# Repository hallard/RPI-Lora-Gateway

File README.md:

Raspberry PI Lora Gateway/Node for RFM92/95/96/98/69HCW Modules
===============================================================

This shield is used to hold one or two HopeRF [Lora module][4] Software with Raspbery PI plus one FM12B/RFM69CW/RFM69(H)W.
it's the parent of the small [LoRasPi][11], so please look at LoRasPi [readme][12] to see features and software links.

This board has been mainly inspired from [Uptronics][14] expansion board on which I added some features but it's not a real LoraWAN concentrator, if you need a real concentrator with multiple channels and fully compliant to LoraWan stack capabilities, please see thethingsnetwork [wiki][1] dedicated to gateways.

By the way, with Lora modules installed on this board you can have it working as a Single Channel Gateway or a LoraWan node. For testing, demo or small projects, it can be enought.

Quick features 
==============

- Placement for two RFM92/95/96/98 Lora module (IE one 868MHz and one 433MHz, or 2 channels 868MHz)
- Placement for one RFM12B/RFM69CW/RFM69(H)W classic module
- Placement for choosing single Wire, SMA, u-FL or Thru Hole PCB Mount (Right Angle Tor straight)
by Eightwood Antenna type
- Vertical Antenna placement is possible (easier to drill RPI top enclosure)
- 4 x LED for visual indication
- Each Module reset pin can be connected to a RPI GPIO

Boards arrived from ElectroDragon, all is working as expected.

Detailed Description
====================

Look at the schematics for more informations.

SPI connexion is classic (MOSI/MISO/CLK), Chip Select is CE0 for Module 1 and CE1 for Module 2. Module 3 can be choosen between CE0 and GPIO26 with on board jumper switch.

```
Raspberry PI   RFM9x Module 1
   CE0     <---->  SEL
   GPIO5   <---->  Reset (JP5)
   GPIO25  <---->  DIO0 
   GPIO24  <---->  DIO5 

Raspberry PI   RFM9x Module 2
   CE1     <---->  SEL
   GPIO6   <---->  Reset (JP6)
   GPIO16  <---->  DIO0 
   GPIO12  <---->  DIO5 

Raspberry PI   RFM69/12 Module 3
 IO26/CE0  <---->  SEL
  GPIO13   <---->  Reset (JP13)
  GPIO23   <---->  DIO0 
  GPIO12   <---->  DIO2

Raspberry PI   On Board LEDS
   GPIO4   <---->  LED 4
   GPIO17  <---->  LED 17
   GPIO18  <---->  LED 18
   GPIO19  <---->  LED 19
```

### Hardware Setup

Nothing really complicated, you can wire Reset of each module on a GPIO pin if you want to be able to hardware reset then using software, in this case put jumper on JP5 for Module 1, JP6 for Module 2 and JP13 for Module 3. JPx number is the GPIO so JP5 is for GPIO5 ;-)

If you want to use Module 1 and Module 3 you need to set JP1 (Chip Select of module 3) to IO26 since CE0 is used by Module 1.

### Software Setup

I'm working on two libraries port and Single Channel Gateway to work on Raspberry PI, links are here   

- [LMIC][15] to be LoraWan compliant.  This LMIC is working with this shield, see [readme][18] of repo.
- Excellent [RadioHead][16] twekaed library for RFM69, RFM9x modules (and lot of others). This version is working with this shield, see [readme][17] of library.
- The Things Network [Single Channel Gateway packet forwarder][24]

I forked all repos to tweak them, but since I'm not sure original authors would like to merge my changes just use my forks. 

For reference, original libraries and code are [Arduino-LIMC][21], [RadioHead-LIMC][23], [Single Channel Gateway packet forwarder][25]

### Schematic  

### Boards  
&nbsp;&nbsp; 

### Received boards 

&nbsp; 

You can order the PCB of this board [PCBs.io][13]. PCBs.io give me some reward when you order my designed boards from their site. This is pretty good, because I can use these rewards to create and design new boards and order boards for a discounted price and share new boards.

### Assembled and mounted board

Here is my testing board, as you can see, 3 modules on it    
- Module 1 (top left) Lora RFM95 868MHz
- Module 2 (bottom left) Lora RFM98 433MHz
- Module 3 (right) RFM69HW 433MHz

##License

You can do whatever you like with this design.

##Misc
See news and other projects on my [blog][2] 

[1]: https://www.thethingsnetwork.org/wiki/Hardware/Gateways/Overview
[2]: https://hallard.me
[4]: http://www.hoperf.com/rf_transceiver/lora/
[5]: https://github.com/hallard/single_chan_pkt_fwd
[6]: http://www.daveakerman.com/?p=1719
[7]: https://store.uputronics.com/index.php?route=product/product&search=lora&product_id=68
[8]: https://PCBs.io/share/zkD74
[9]: https://github.com/matthijskooijman/arduino-lmic/
[10]: https://github.com/hallard/RadioHead
[11]: https://github.com/hallard/LoRasPI
[12]: https://github.com/hallard/LoRasPI/blob/master/README.md
[13]: https://PCBs.io/share/zvxQ8
[14]: https://store.uputronics.com/index.php?route=product/product&search=lora&product_id=68

[15]: https://github.com/hallard/arduino-lmic/tree/rpi
[16]: https://github.com/hallard/RadioHead
[17]: https://github.com/hallard/RadioHead/blob/master/README.md
[18]: https://github.com/hallard/arduino-lmic/blob/rpi/README.md

[20]: https://github.com/hallard/arduino-lmic
[21]: https://github.com/matthijskooijman/arduino-lmic
[22]: https://github.com/hallard/RadioHead
[23]: http://www.airspayce.com/mikem/arduino/RadioHead/
[24]: https://github.com/hallard/single_chan_pkt_fwd
[25]: https://github.com/jlesech/single_chan_pkt_fwd

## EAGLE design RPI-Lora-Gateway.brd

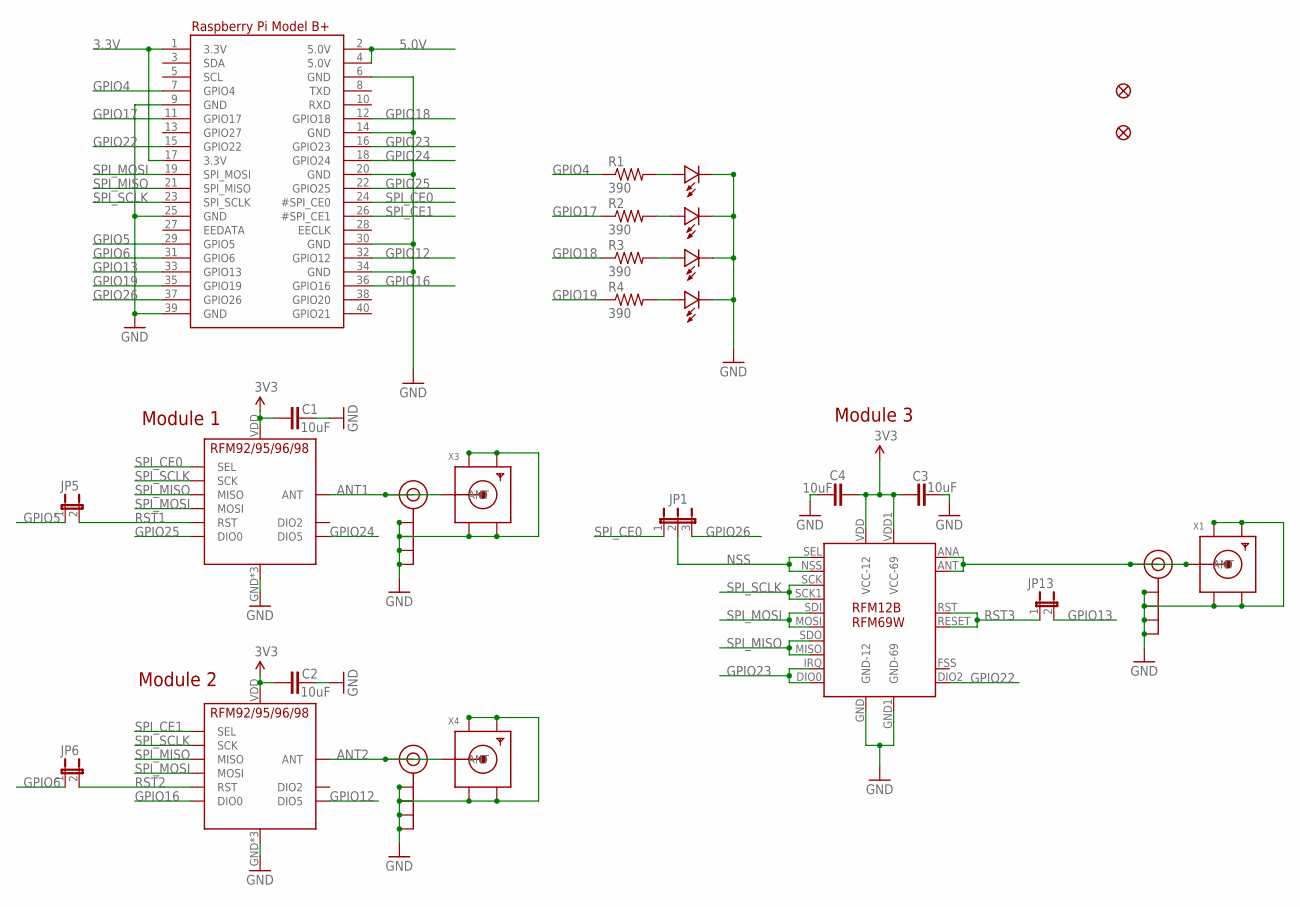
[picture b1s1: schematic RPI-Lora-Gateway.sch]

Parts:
C1, C2, C3, C4: 10uF; 0805-CAP
FID2, FID3: FIDUCIAL""; FIDUCIAL_1MM
J$1, J$2, J$3: ANTENNATINY; SMA_UFL_PAD_TINY
JP1: JUMPER3
JP5, JP6, JP13: JUMPER2
R1, R2, R3, R4: 390; 0805-RES
RPI1: RASPBERRYPI_BPLUS_HATNOSLOTS; PI_HAT_NOSLOTS
U$1, U$2: RFM95
U$3: RFM-DUAL
U$4: IO4; 0805-LED
U$5: IO17; 0805-LED
U$6: IO18; 0805-LED
U$7: IO19; 0805-LED
X1, X3, X4: SMACONNECTOR; SMA90_DIP

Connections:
3.3V: C1.1, C2.1, C3.1, C4.1, RPI1.1 (3.3V), RPI1.17 (3.3V), U$1.VDD (VCC), U$2.VDD (VCC), U$3.VDD (VCC-12), U$3.VDD1 (VCC-69)
5.0V: RPI1.2 (5.0V), RPI1.4 (5.0V)
ANT1: J$1.ANT1 (SIGNAL), J$1.ANT2 (SIGNAL), J$1.ANT3 (SIGNAL), U$1.ANT, X3.ANTENNA (ANT)
ANT2: J$2.ANT1 (SIGNAL), J$2.ANT2 (SIGNAL), J$2.ANT3 (SIGNAL), U$2.ANT, X4.ANTENNA (ANT)
GND: C1.2, C2.2, C3.2, C4.2, J$1.GND1 (GND), J$1.GND2 (GND), J$1.GND3 (GND), J$1.GND4 (GND), J$2.GND1 (GND), J$2.GND2 (GND), J$2.GND3 (GND), J$2.GND4 (GND), J$3.GND1 (GND), J$3.GND2 (GND), J$3.GND3 (GND), J$3.GND4 (GND), RPI1.6 (GND), RPI1.9 (GND), RPI1.14 (GND), RPI1.20 (GND), RPI1.25 (GND), RPI1.30 (GND), RPI1.34 (GND), RPI1.39 (GND), U$1.GND, U$1.GND1 (GND), U$1.GND2 (GND), U$2.GND, U$2.GND1 (GND), U$2.GND2 (GND), U$3.GND (GND-12), U$3.GND1 (GND-69), U$4.MINUS, U$5.MINUS, U$6.MINUS, U$7.MINUS, X1.GND1, X1.GND2, X1.GND3, X1.GND4, X3.GND1, X3.GND2, X3.GND3, X3.GND4, X4.GND1, X4.GND2, X4.GND3, X4.GND4
GPIO4: R1.1, RPI1.7 (GPIO4)
GPIO5: JP5.1, RPI1.29 (GPIO5)
GPIO6: JP6.1, RPI1.31 (GPIO6)
GPIO12: RPI1.32 (GPIO12), U$2.DIO5
GPIO13: JP13.2, RPI1.33 (GPIO13)
GPIO16: RPI1.36 (GPIO16), U$2.DIO0
GPIO17: R2.1, RPI1.11 (GPIO17)
GPIO18: R3.1, RPI1.12 (GPIO18)
GPIO19: R4.1, RPI1.35 (GPIO19)
GPIO22: RPI1.15 (GPIO22), U$3.DIO2
GPIO23: RPI1.16 (GPIO23), U$3.DIO0, U$3.IRQ
GPIO24: RPI1.18 (GPIO24), U$1.DIO5
GPIO25: RPI1.22 (GPIO25), U$1.DIO0
GPIO26: JP1.3, RPI1.37 (GPIO26)
unnamed: J$3.ANT1 (SIGNAL), J$3.ANT2 (SIGNAL), J$3.ANT3 (SIGNAL), U$3.ANA (ANT-12), U$3.ANT (ANT-69), X1.ANTENNA (ANT)
unnamed: R4.2, U$7.PLUS
unnamed: R1.2, U$4.PLUS
unnamed: R2.2, U$5.PLUS
unnamed: R3.2, U$6.PLUS
NSS: JP1.2, U$3.NSS (SEL-12), U$3.SEL (SEL-69)
RST1: JP5.2, U$1.RST
RST2: JP6.2, U$2.RST
RST3: JP13.1, U$3.RESET, U$3.RST
SPI_CE0: JP1.1, RPI1.24 (#SPI_CE0), U$1.NSS (SEL)
SPI_CE1: RPI1.26 (#SPI_CE1), U$2.NSS (SEL)
SPI_MISO: RPI1.21 (SPI_MISO), U$1.MISO, U$2.MISO, U$3.MISO, U$3.SDO
SPI_MOSI: RPI1.19 (SPI_MOSI), U$1.MOSI, U$2.MOSI, U$3.MOSI, U$3.SDI
SPI_SCLK: RPI1.23 (SPI_SCLK), U$1.SCK, U$2.SCK, U$3.SCK, U$3.SCK1

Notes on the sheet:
Module 1
Module 2
Module 3

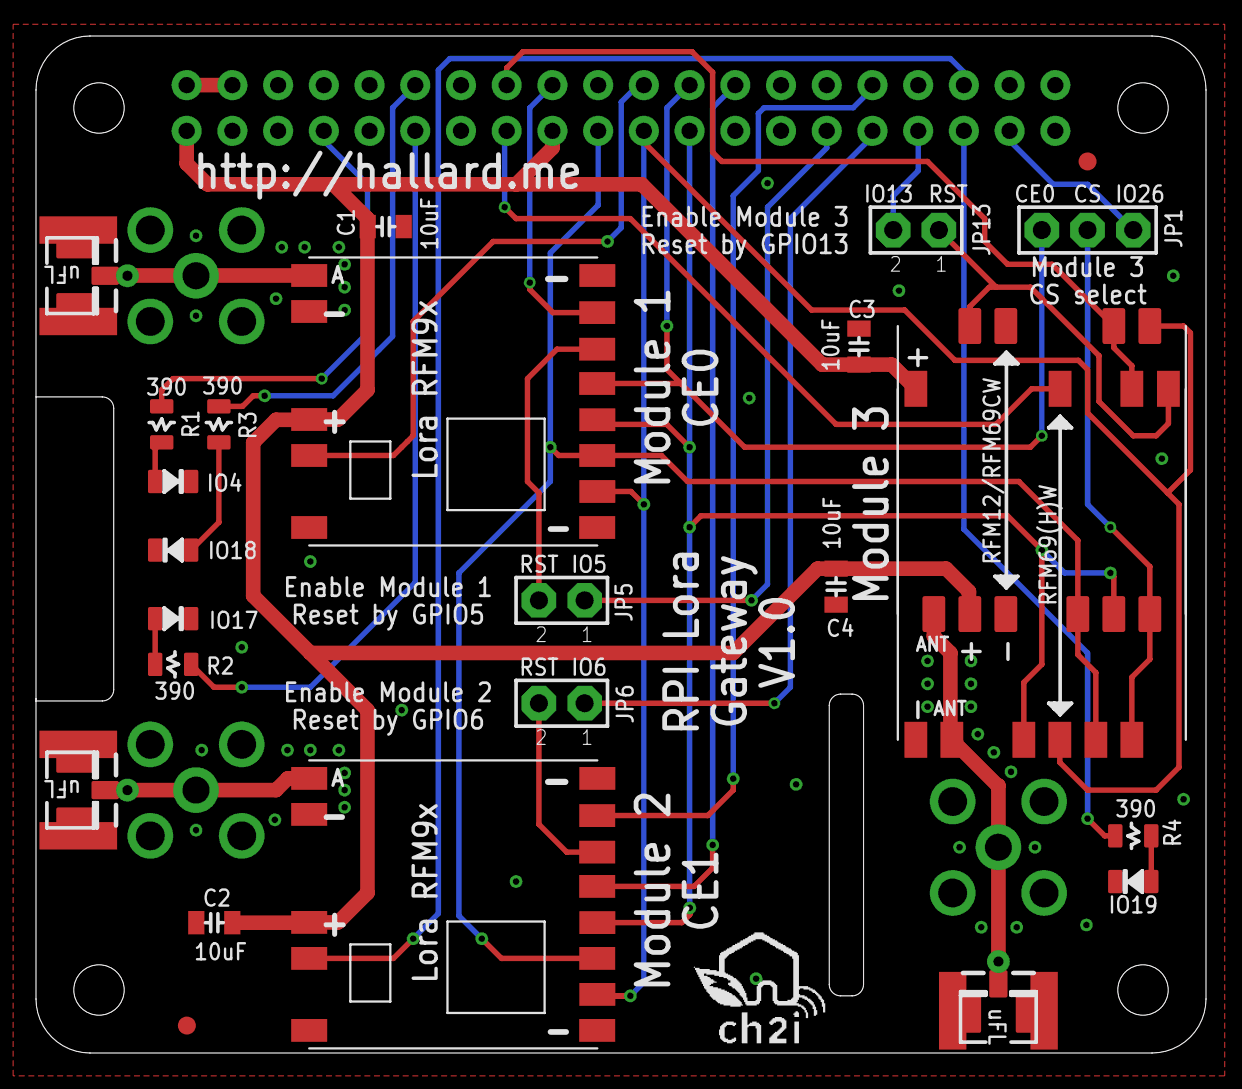
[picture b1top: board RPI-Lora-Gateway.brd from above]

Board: 2 copper layers, 65.0 x 56.5 mm, 30 parts (1 on the bottom side), 33 nets.

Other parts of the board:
U$8: LOGO_CH2I_75MM
U$9: LOGO_CH2I_110MM

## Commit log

2016-08-06 :space_invader: Added .gitattributes
2016-08-06 Creation
2016-08-06 Link on ElectroDrago Boards
2016-08-06 Added uptronics reference
2016-08-12 Added pictures and links
2016-08-12 Chnaged image size
2016-08-12 Added links to code
2016-08-12 Type
2016-08-12 presentation
2016-08-12 Image resize
2016-09-21 Added link to software

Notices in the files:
parts and their libraries:
microbuilder: This work is placed in the public domain, and may be freely used for commercial and non-commercial work with the following conditions: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
SparkFun-Aesthetics: Licensing: Creative Commons ShareAlike 4.0 International - https://creativecommons.org/licenses/by-sa/4.0
